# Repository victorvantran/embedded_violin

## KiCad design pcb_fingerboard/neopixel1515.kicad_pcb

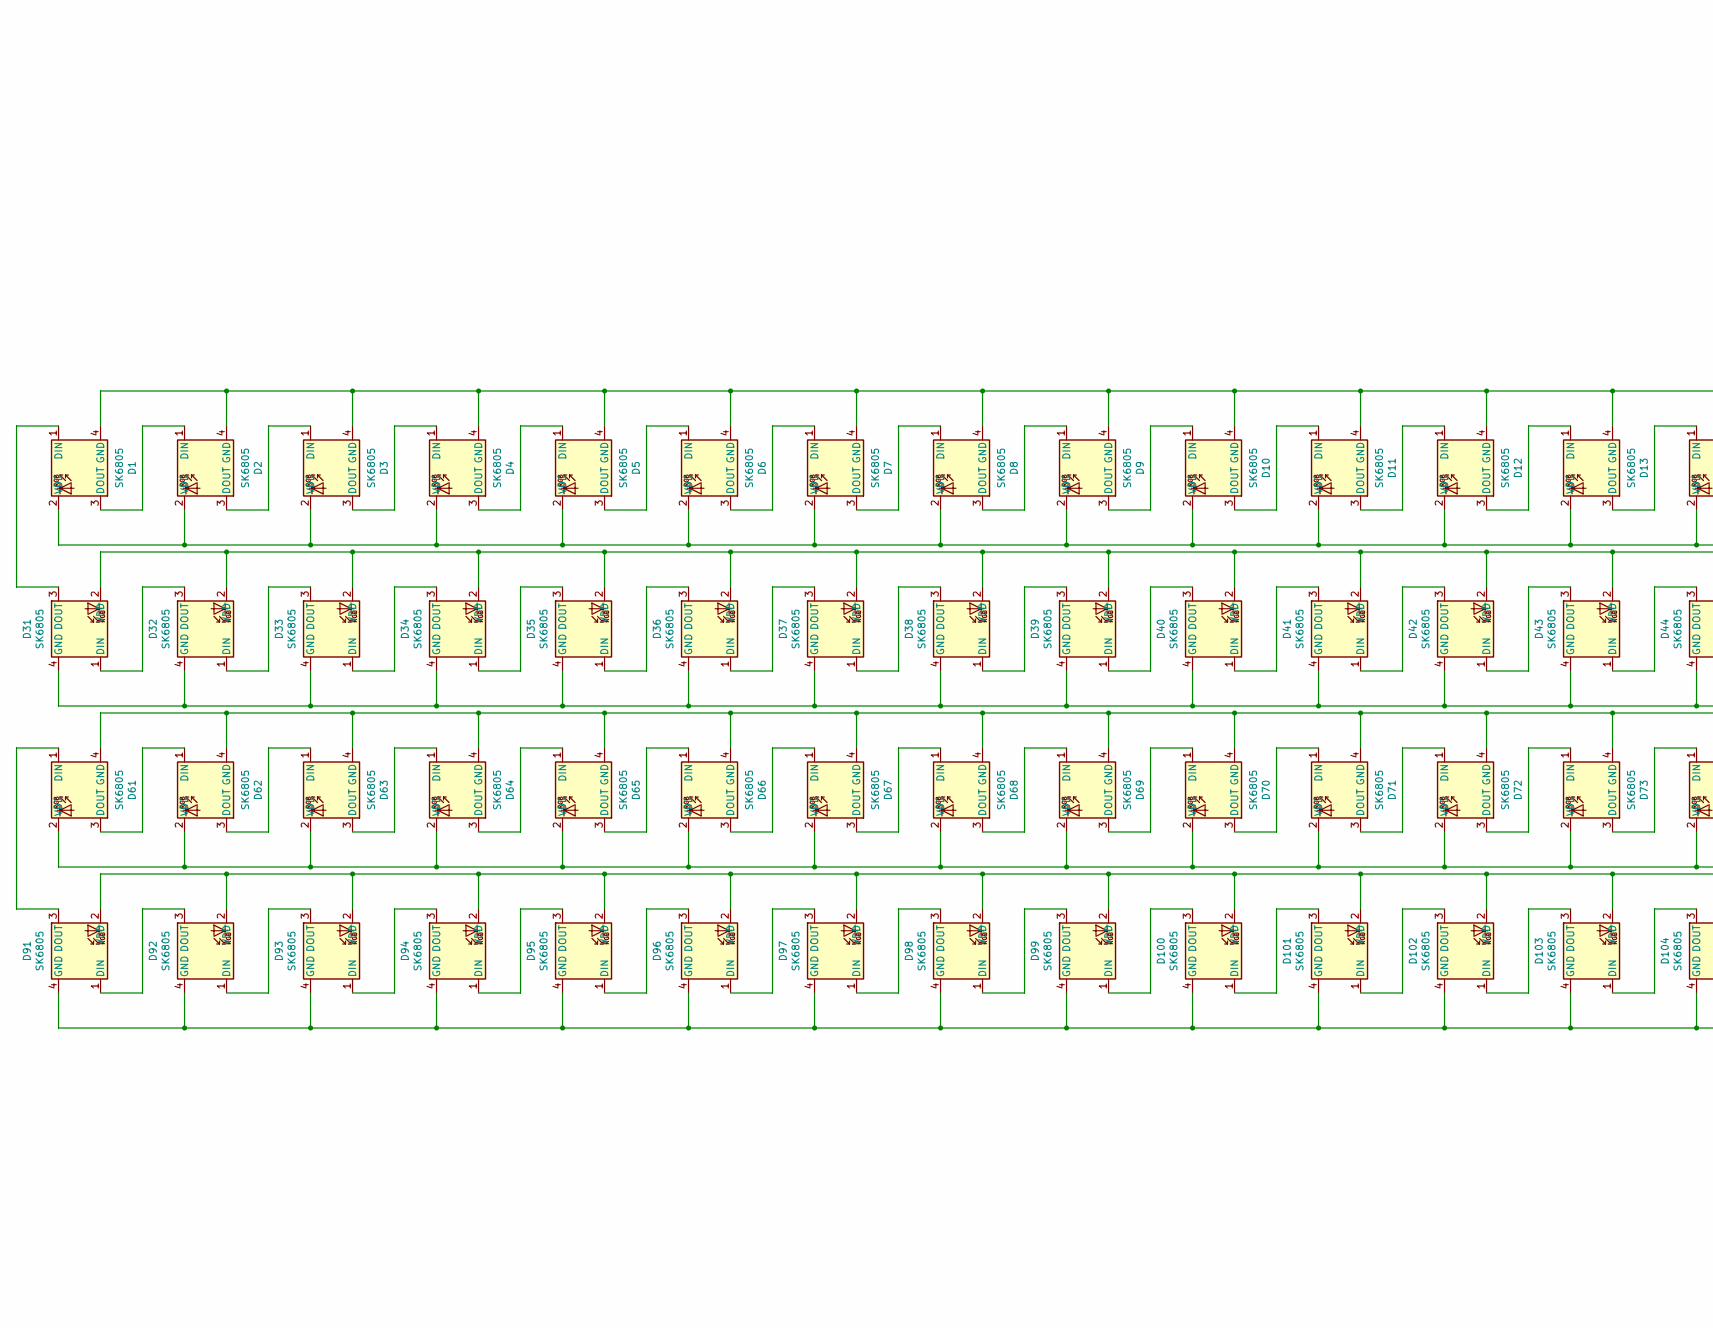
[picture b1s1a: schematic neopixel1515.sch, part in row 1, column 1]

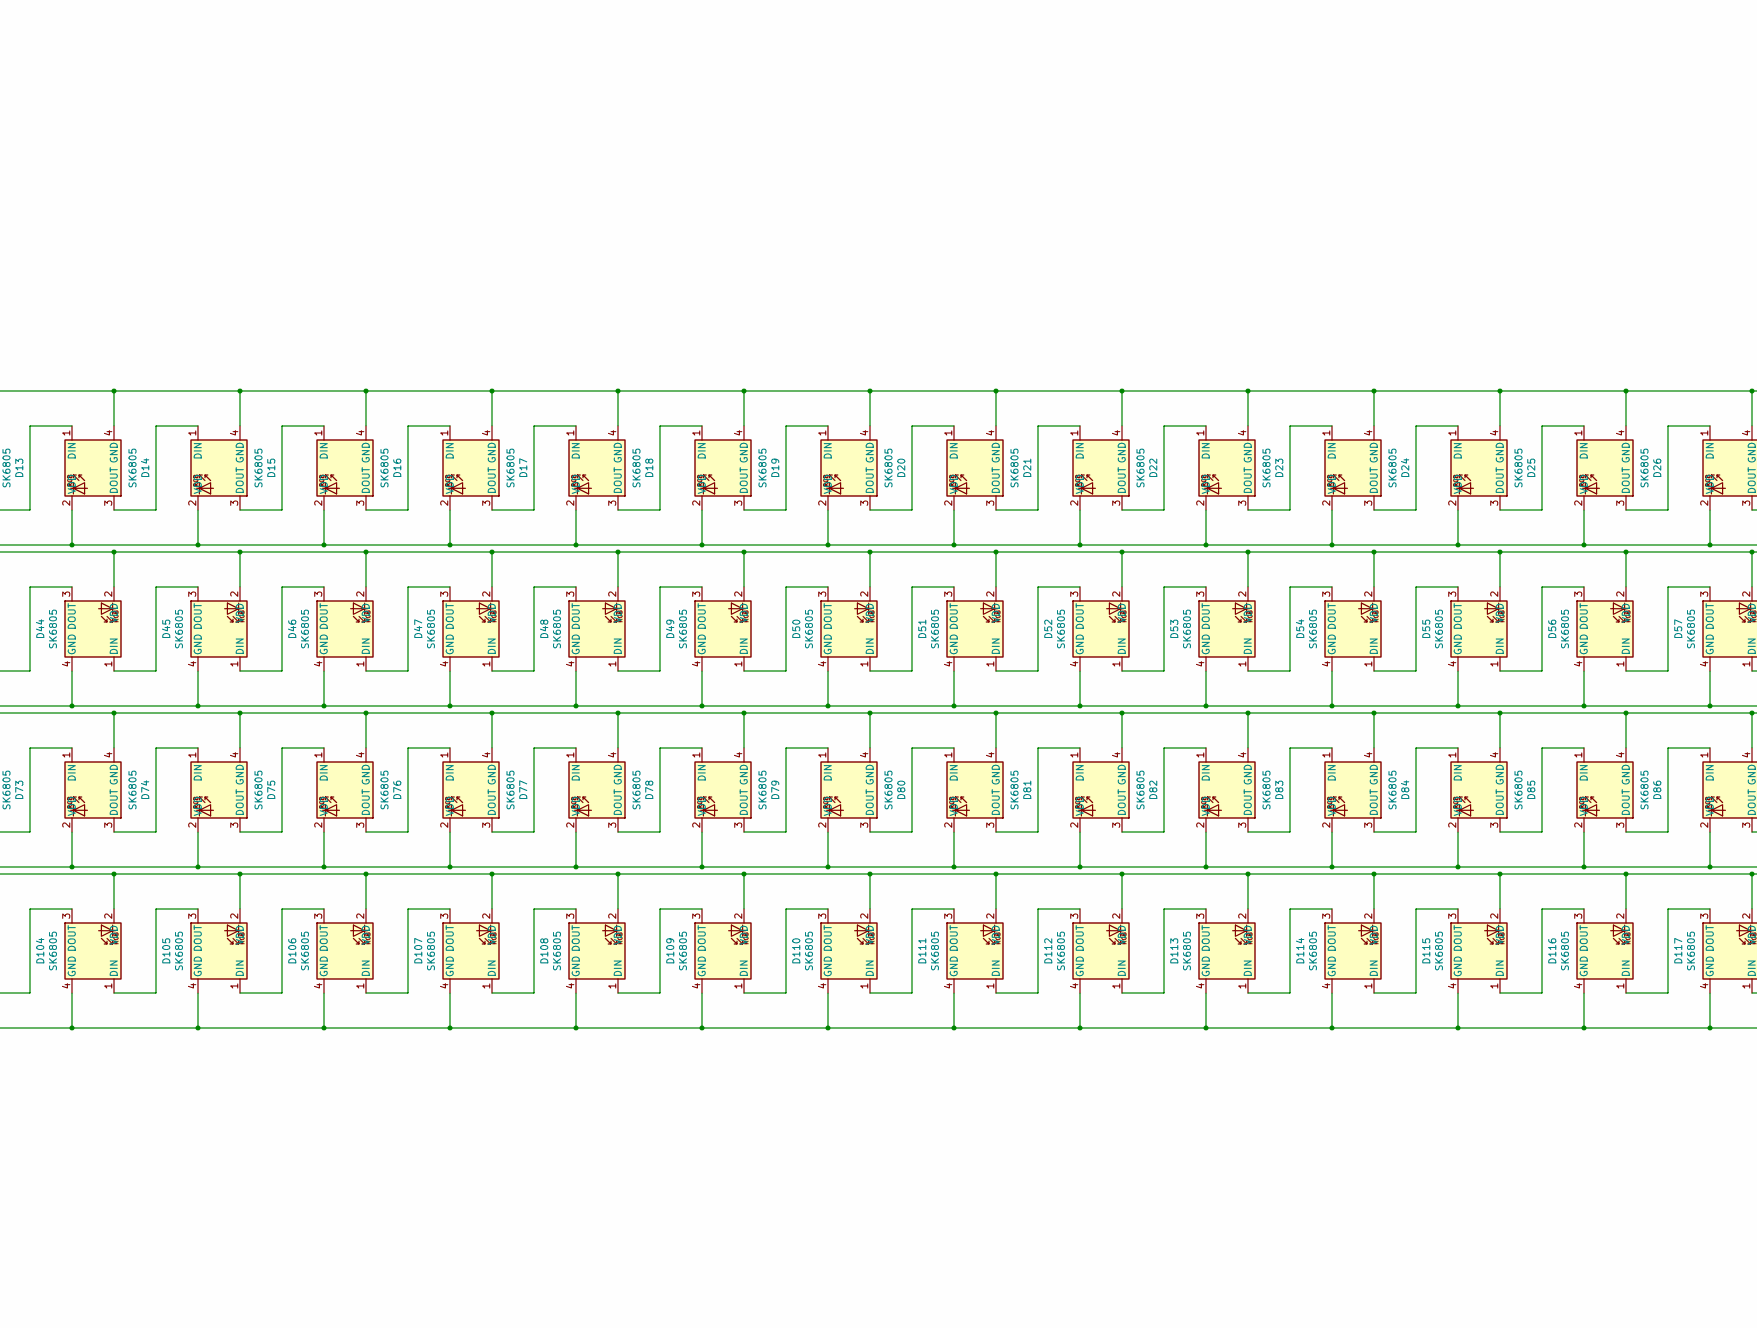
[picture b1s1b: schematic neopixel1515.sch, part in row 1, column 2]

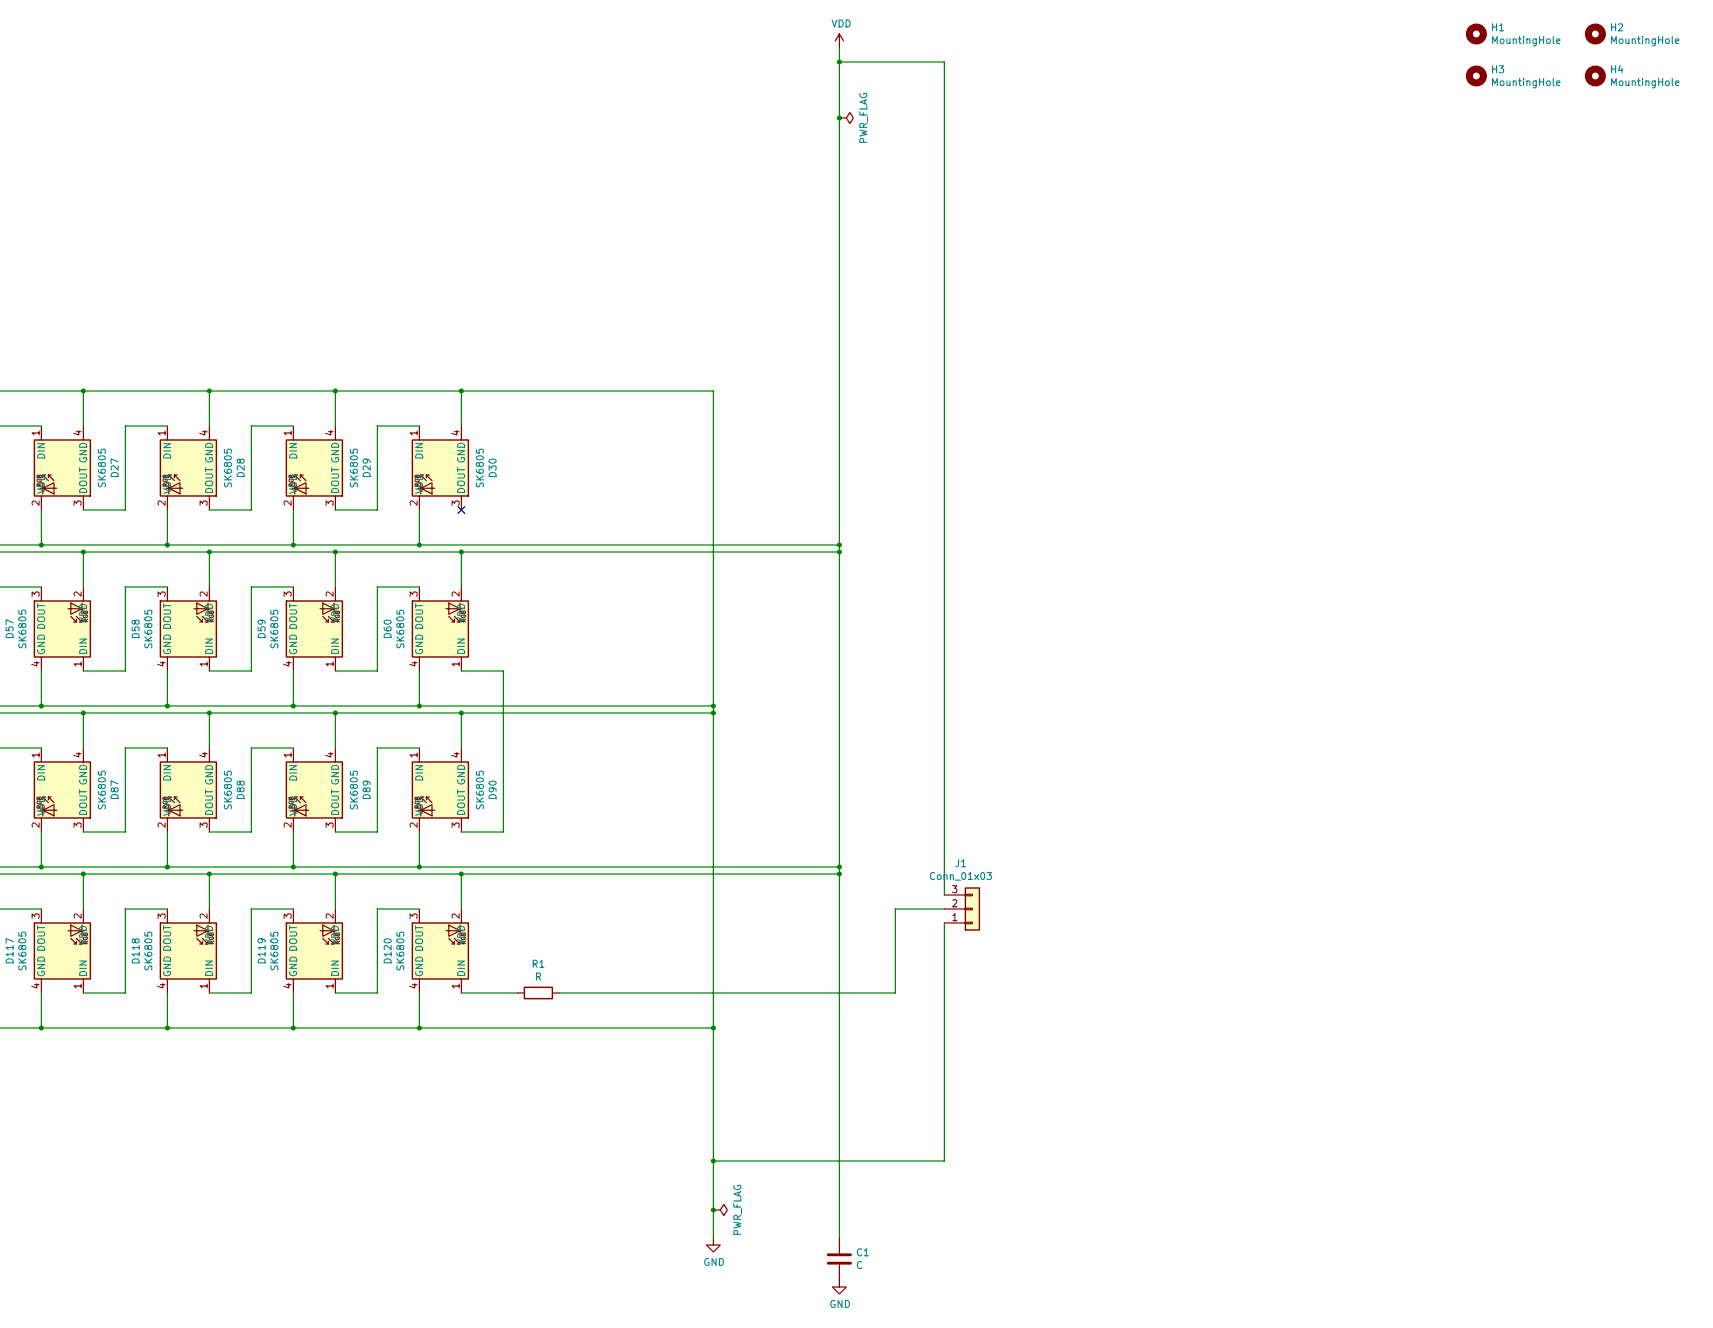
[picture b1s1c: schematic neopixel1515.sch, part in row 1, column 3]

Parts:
C1: C; CP_Radial_D10.0mm_P5.00mm
D1, D2, D3, D4, D5, D6, D7, D8, D9, D10, D11, D12, D13, D14, D15, D16, D17, D18, D19, D20, D21, D22, D23, D24, D25, D26, D27, D28, D29, D30, D31, D32, D33, D34, D35, D36, D37, D38, D39, D40, D41, D42, D43, D44, D45, D46, D47, D48, D49, D50, D51, D52, D53, D54, D55, D56, D57, D58, D59, D60, D61, D62, D63, D64, D65, D66, D67, D68, D69, D70, D71, D72, D73, D74, D75, D76, D77, D78, D79, D80, D81, D82, D83, D84, D85, D86, D87, D88, D89, D90, D91, D92, D93, D94, D95, D96, D97, D98, D99, D100, D101, D102, D103, D104, D105, D106, D107, D108, D109, D110, D111, D112, D113, D114, D115, D116, D117, D118, D119, D120: SK6805; LED_SK6812_EC15_1.5x1.5mm
H1, H2, H3, H4: MountingHole; MountingHole_3.2mm_M3
J1: Conn_01x03; PinHeader_1x03_P2.54mm_Horizontal
R1: R; R_0805_2012Metric_Pad1.20x1.40mm_HandSolder

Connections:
GND: C1.2, D1.4 (GND), D2.4 (GND), D3.4 (GND), D4.4 (GND), D5.4 (GND), D6.4 (GND), D7.4 (GND), D8.4 (GND), D9.4 (GND), D10.4 (GND), D11.4 (GND), D12.4 (GND), D13.4 (GND), D14.4 (GND), D15.4 (GND), D16.4 (GND), D17.4 (GND), D18.4 (GND), D19.4 (GND), D20.4 (GND), D21.4 (GND), D22.4 (GND), D23.4 (GND), D24.4 (GND), D25.4 (GND), D26.4 (GND), D27.4 (GND), D28.4 (GND), D29.4 (GND), D30.4 (GND), D31.4 (GND), D32.4 (GND), D33.4 (GND), D34.4 (GND), D35.4 (GND), D36.4 (GND), D37.4 (GND), D38.4 (GND), D39.4 (GND), D40.4 (GND), D41.4 (GND), D42.4 (GND), D43.4 (GND), D44.4 (GND), D45.4 (GND), D46.4 (GND), D47.4 (GND), D48.4 (GND), D49.4 (GND), D50.4 (GND), D51.4 (GND), D52.4 (GND), D53.4 (GND), D54.4 (GND), D55.4 (GND), D56.4 (GND), D57.4 (GND), D58.4 (GND), D59.4 (GND), D60.4 (GND), D61.4 (GND), D62.4 (GND), D63.4 (GND), D64.4 (GND), D65.4 (GND), D66.4 (GND), D67.4 (GND), D68.4 (GND), D69.4 (GND), D70.4 (GND), D71.4 (GND), D72.4 (GND), D73.4 (GND), D74.4 (GND), D75.4 (GND), D76.4 (GND), D77.4 (GND), D78.4 (GND), D79.4 (GND), D80.4 (GND), D81.4 (GND), D82.4 (GND), D83.4 (GND), D84.4 (GND), D85.4 (GND), D86.4 (GND), D87.4 (GND), D88.4 (GND), D89.4 (GND), D90.4 (GND), D91.4 (GND), D92.4 (GND), D93.4 (GND), D94.4 (GND), D95.4 (GND), D96.4 (GND), D97.4 (GND), D98.4 (GND), D99.4 (GND), D100.4 (GND), D101.4 (GND), D102.4 (GND), D103.4 (GND), D104.4 (GND), D105.4 (GND), D106.4 (GND), D107.4 (GND), D108.4 (GND), D109.4 (GND), D110.4 (GND), D111.4 (GND), D112.4 (GND), D113.4 (GND), D114.4 (GND), D115.4 (GND), D116.4 (GND), D117.4 (GND), D118.4 (GND), D119.4 (GND), D120.4 (GND), H1.1, H2.1, H3.1, H4.1, J1.1
unnamed: D1.1 (DIN), D31.3 (DOUT)
unnamed: D1.3 (DOUT), D2.1 (DIN)
unnamed: D2.3 (DOUT), D3.1 (DIN)
unnamed: D3.3 (DOUT), D4.1 (DIN)
unnamed: D4.3 (DOUT), D5.1 (DIN)
unnamed: D5.3 (DOUT), D6.1 (DIN)
unnamed: D6.3 (DOUT), D7.1 (DIN)
unnamed: D7.3 (DOUT), D8.1 (DIN)
unnamed: D8.3 (DOUT), D9.1 (DIN)
unnamed: D9.3 (DOUT), D10.1 (DIN)
unnamed: D10.3 (DOUT), D11.1 (DIN)
unnamed: D11.3 (DOUT), D12.1 (DIN)
unnamed: D12.3 (DOUT), D13.1 (DIN)
unnamed: D13.3 (DOUT), D14.1 (DIN)
unnamed: D14.3 (DOUT), D15.1 (DIN)
unnamed: D15.3 (DOUT), D16.1 (DIN)
unnamed: D16.3 (DOUT), D17.1 (DIN)
unnamed: D17.3 (DOUT), D18.1 (DIN)
unnamed: D18.3 (DOUT), D19.1 (DIN)
unnamed: D19.3 (DOUT), D20.1 (DIN)
unnamed: D20.3 (DOUT), D21.1 (DIN)
unnamed: D21.3 (DOUT), D22.1 (DIN)
unnamed: D22.3 (DOUT), D23.1 (DIN)
unnamed: D23.3 (DOUT), D24.1 (DIN)
unnamed: D24.3 (DOUT), D25.1 (DIN)
unnamed: D25.3 (DOUT), D26.1 (DIN)
unnamed: D26.3 (DOUT), D27.1 (DIN)
unnamed: D27.3 (DOUT), D28.1 (DIN)
unnamed: D28.3 (DOUT), D29.1 (DIN)
unnamed: D29.3 (DOUT), D30.1 (DIN)
unnamed: D31.1 (DIN), D32.3 (DOUT)
unnamed: D32.1 (DIN), D33.3 (DOUT)
unnamed: D33.1 (DIN), D34.3 (DOUT)
unnamed: D34.1 (DIN), D35.3 (DOUT)
unnamed: D35.1 (DIN), D36.3 (DOUT)
unnamed: D36.1 (DIN), D37.3 (DOUT)
unnamed: D37.1 (DIN), D38.3 (DOUT)
unnamed: D38.1 (DIN), D39.3 (DOUT)
unnamed: D39.1 (DIN), D40.3 (DOUT)
unnamed: D40.1 (DIN), D41.3 (DOUT)
unnamed: D41.1 (DIN), D42.3 (DOUT)
unnamed: D42.1 (DIN), D43.3 (DOUT)
unnamed: D43.1 (DIN), D44.3 (DOUT)
unnamed: D44.1 (DIN), D45.3 (DOUT)
unnamed: D45.1 (DIN), D46.3 (DOUT)
unnamed: D46.1 (DIN), D47.3 (DOUT)
unnamed: D47.1 (DIN), D48.3 (DOUT)
unnamed: D48.1 (DIN), D49.3 (DOUT)
unnamed: D49.1 (DIN), D50.3 (DOUT)
unnamed: D50.1 (DIN), D51.3 (DOUT)
unnamed: D51.1 (DIN), D52.3 (DOUT)
unnamed: D52.1 (DIN), D53.3 (DOUT)
unnamed: D53.1 (DIN), D54.3 (DOUT)
unnamed: D54.1 (DIN), D55.3 (DOUT)
unnamed: D55.1 (DIN), D56.3 (DOUT)
unnamed: D56.1 (DIN), D57.3 (DOUT)
unnamed: D57.1 (DIN), D58.3 (DOUT)
unnamed: D58.1 (DIN), D59.3 (DOUT)
unnamed: D59.1 (DIN), D60.3 (DOUT)
unnamed: D60.1 (DIN), D90.3 (DOUT)
unnamed: D61.1 (DIN), D91.3 (DOUT)
unnamed: D61.3 (DOUT), D62.1 (DIN)
unnamed: D62.3 (DOUT), D63.1 (DIN)
unnamed: D63.3 (DOUT), D64.1 (DIN)
unnamed: D64.3 (DOUT), D65.1 (DIN)
unnamed: D65.3 (DOUT), D66.1 (DIN)
unnamed: D66.3 (DOUT), D67.1 (DIN)
unnamed: D67.3 (DOUT), D68.1 (DIN)
unnamed: D68.3 (DOUT), D69.1 (DIN)
unnamed: D69.3 (DOUT), D70.1 (DIN)
unnamed: D70.3 (DOUT), D71.1 (DIN)
unnamed: D71.3 (DOUT), D72.1 (DIN)
unnamed: D72.3 (DOUT), D73.1 (DIN)
unnamed: D73.3 (DOUT), D74.1 (DIN)
unnamed: D74.3 (DOUT), D75.1 (DIN)
unnamed: D75.3 (DOUT), D76.1 (DIN)
unnamed: D76.3 (DOUT), D77.1 (DIN)
unnamed: D77.3 (DOUT), D78.1 (DIN)
unnamed: D78.3 (DOUT), D79.1 (DIN)
unnamed: D79.3 (DOUT), D80.1 (DIN)
unnamed: D80.3 (DOUT), D81.1 (DIN)
unnamed: D81.3 (DOUT), D82.1 (DIN)
unnamed: D82.3 (DOUT), D83.1 (DIN)
unnamed: D83.3 (DOUT), D84.1 (DIN)
unnamed: D84.3 (DOUT), D85.1 (DIN)
unnamed: D85.3 (DOUT), D86.1 (DIN)
unnamed: D86.3 (DOUT), D87.1 (DIN)
unnamed: D87.3 (DOUT), D88.1 (DIN)
unnamed: D88.3 (DOUT), D89.1 (DIN)
unnamed: D89.3 (DOUT), D90.1 (DIN)
unnamed: D91.1 (DIN), D92.3 (DOUT)
unnamed: D92.1 (DIN), D93.3 (DOUT)
unnamed: D93.1 (DIN), D94.3 (DOUT)
unnamed: D94.1 (DIN), D95.3 (DOUT)
unnamed: D95.1 (DIN), D96.3 (DOUT)
unnamed: D96.1 (DIN), D97.3 (DOUT)
unnamed: D97.1 (DIN), D98.3 (DOUT)
unnamed: D98.1 (DIN), D99.3 (DOUT)
unnamed: D100.1 (DIN), D101.3 (DOUT)
unnamed: D99.1 (DIN), D100.3 (DOUT)
unnamed: D101.1 (DIN), D102.3 (DOUT)
unnamed: D102.1 (DIN), D103.3 (DOUT)
unnamed: D103.1 (DIN), D104.3 (DOUT)
unnamed: D104.1 (DIN), D105.3 (DOUT)
unnamed: D105.1 (DIN), D106.3 (DOUT)
unnamed: D106.1 (DIN), D107.3 (DOUT)
unnamed: D107.1 (DIN), D108.3 (DOUT)
unnamed: D108.1 (DIN), D109.3 (DOUT)
unnamed: D109.1 (DIN), D110.3 (DOUT)
unnamed: D110.1 (DIN), D111.3 (DOUT)
unnamed: D111.1 (DIN), D112.3 (DOUT)
unnamed: D112.1 (DIN), D113.3 (DOUT)
unnamed: D113.1 (DIN), D114.3 (DOUT)
unnamed: D114.1 (DIN), D115.3 (DOUT)
unnamed: D115.1 (DIN), D116.3 (DOUT)
unnamed: D116.1 (DIN), D117.3 (DOUT)
unnamed: D117.1 (DIN), D118.3 (DOUT)
unnamed: D118.1 (DIN), D119.3 (DOUT)
unnamed: D119.1 (DIN), D120.3 (DOUT)
unnamed: D120.1 (DIN), R1.1
unnamed: J1.2, R1.2
VDD: C1.1, D1.2 (VDD), D2.2 (VDD), D3.2 (VDD), D4.2 (VDD), D5.2 (VDD), D6.2 (VDD), D7.2 (VDD), D8.2 (VDD), D9.2 (VDD), D10.2 (VDD), D11.2 (VDD), D12.2 (VDD), D13.2 (VDD), D14.2 (VDD), D15.2 (VDD), D16.2 (VDD), D17.2 (VDD), D18.2 (VDD), D19.2 (VDD), D20.2 (VDD), D21.2 (VDD), D22.2 (VDD), D23.2 (VDD), D24.2 (VDD), D25.2 (VDD), D26.2 (VDD), D27.2 (VDD), D28.2 (VDD), D29.2 (VDD), D30.2 (VDD), D31.2 (VDD), D32.2 (VDD), D33.2 (VDD), D34.2 (VDD), D35.2 (VDD), D36.2 (VDD), D37.2 (VDD), D38.2 (VDD), D39.2 (VDD), D40.2 (VDD), D41.2 (VDD), D42.2 (VDD), D43.2 (VDD), D44.2 (VDD), D45.2 (VDD), D46.2 (VDD), D47.2 (VDD), D48.2 (VDD), D49.2 (VDD), D50.2 (VDD), D51.2 (VDD), D52.2 (VDD), D53.2 (VDD), D54.2 (VDD), D55.2 (VDD), D56.2 (VDD), D57.2 (VDD), D58.2 (VDD), D59.2 (VDD), D60.2 (VDD), D61.2 (VDD), D62.2 (VDD), D63.2 (VDD), D64.2 (VDD), D65.2 (VDD), D66.2 (VDD), D67.2 (VDD), D68.2 (VDD), D69.2 (VDD), D70.2 (VDD), D71.2 (VDD), D72.2 (VDD), D73.2 (VDD), D74.2 (VDD), D75.2 (VDD), D76.2 (VDD), D77.2 (VDD), D78.2 (VDD), D79.2 (VDD), D80.2 (VDD), D81.2 (VDD), D82.2 (VDD), D83.2 (VDD), D84.2 (VDD), D85.2 (VDD), D86.2 (VDD), D87.2 (VDD), D88.2 (VDD), D89.2 (VDD), D90.2 (VDD), D91.2 (VDD), D92.2 (VDD), D93.2 (VDD), D94.2 (VDD), D95.2 (VDD), D96.2 (VDD), D97.2 (VDD), D98.2 (VDD), D99.2 (VDD), D100.2 (VDD), D101.2 (VDD), D102.2 (VDD), D103.2 (VDD), D104.2 (VDD), D105.2 (VDD), D106.2 (VDD), D107.2 (VDD), D108.2 (VDD), D109.2 (VDD), D110.2 (VDD), D111.2 (VDD), D112.2 (VDD), D113.2 (VDD), D114.2 (VDD), D115.2 (VDD), D116.2 (VDD), D117.2 (VDD), D118.2 (VDD), D119.2 (VDD), D120.2 (VDD), J1.3

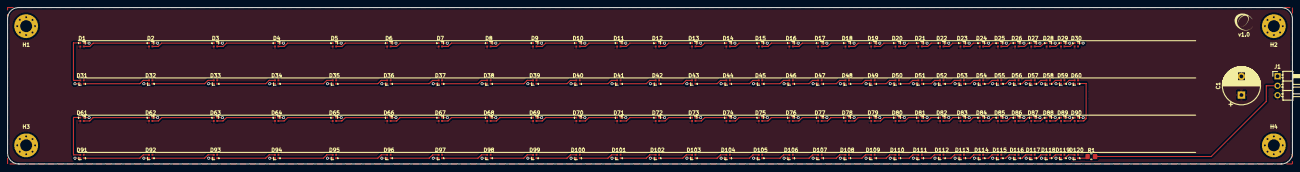
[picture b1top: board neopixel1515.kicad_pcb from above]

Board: 2 copper layers, 345.0 x 42.0 mm, 127 parts (0 on the bottom side), 123 nets.

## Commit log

2021-05-19 Added two speaker with separate PWM timers, and fixed ADC data transmission through UART
2021-05-21 Adjusted moving average filter
2021-05-21 Calibrated fingerboard, updated pull-down resistor
2021-05-21 Established timer overflow interrupt to smooth pitch change
2021-06-15 Integrating microsd via spi
2021-06-15 Synchronized with event groups
2021-06-15 Event group error bit check
2021-06-15 Fixed synch by allocating more memory to heap for tasks using configHEAP...
2021-06-16 Change violin goal processing
2021-06-17 Established Piece Maker software for efficient debugging purposes and future piece writer
2021-06-17 Verified 4 pwm channels
2021-06-19 Established ws2812b driver
2021-06-19 Established light
2021-06-20 Temporary remove busy wait on pwm dma
2021-06-21 Removed extraneous debugging files
2021-06-21 Established fingerbaord pcb
2021-06-21 Layout fingerboard dimension
2021-06-22 Established ADC multichannel DMA
2021-06-22 Pre-print fingerboard pcb
2021-06-22 Added padded mounting holes with vias
2021-06-26 Organize directories
2021-06-26 Established pcb violin
2021-06-28 Mapped finger index
2021-06-29 Cleaning fingering offset
2021-06-30 Commented on piece functions
2021-07-01 PCB update power pins
2021-07-02 Considering MAX604 LDO Voltage Regulator
2021-07-06 Crude fingering light test
2021-07-07 Established violin class
2021-07-08 Transfering auxiliary piece information to violin
2021-07-23 Changing DMA call to neopixel
2021-07-25 Testing other dma channels
